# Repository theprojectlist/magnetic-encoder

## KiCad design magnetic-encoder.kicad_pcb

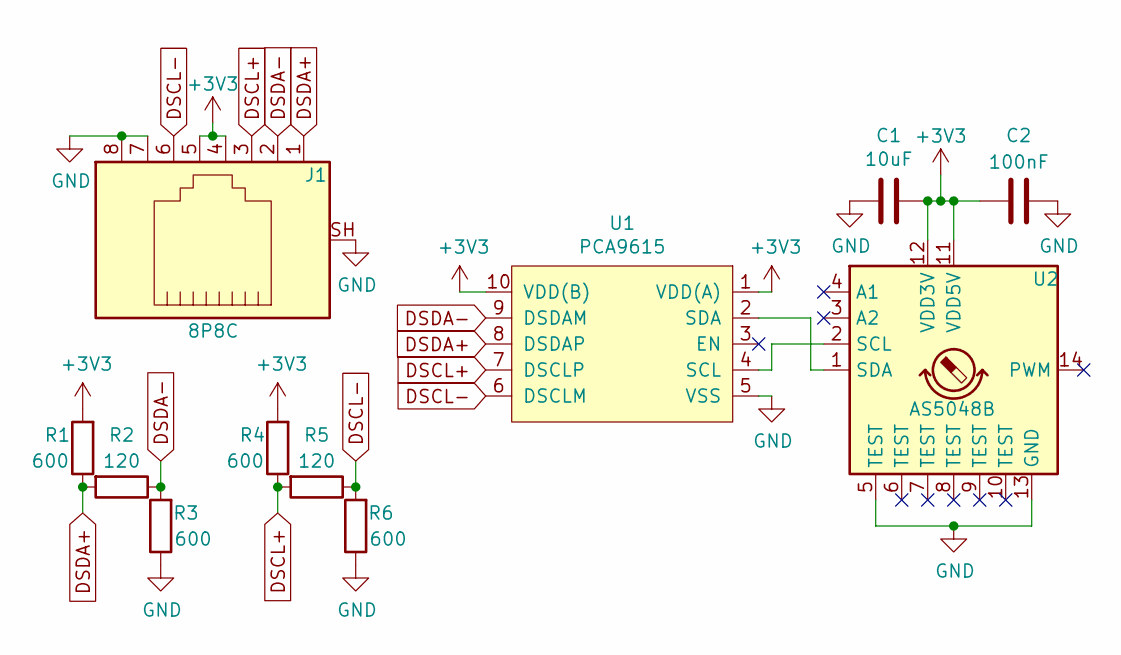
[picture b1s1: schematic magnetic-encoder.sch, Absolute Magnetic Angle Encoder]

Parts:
C1: 10uF; C_0603_1608Metric_Pad1.05x0.95mm_HandSolder
C2: 100nF; C_0603_1608Metric_Pad1.05x0.95mm_HandSolder
J1: 8P8C; RJ45_Amphenol_RJHSE5380
R1, R3, R4, R6: 600; R_0603_1608Metric_Pad1.05x0.95mm_HandSolder
R2, R5: 120; R_0603_1608Metric_Pad1.05x0.95mm_HandSolder
U1: PCA9615; TSSOP-10_3x3mm_P0.5mm
U2: AS5048B; TSSOP-14_4.4x5mm_P0.65mm

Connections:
+3V3: C1.1, C2.2, J1.4, J1.5, R1.2, R4.2, U1.1 (VDD(A)), U1.10 (VDD(B)), U2.11 (VDD5V), U2.12 (VDD3V)
DSCL+: J1.3, R4.1, R5.2, U1.7 (DSCLP)
DSCL-: J1.6, R5.1, R6.2, U1.6 (DSCLM)
DSDA+: J1.1, R1.1, R2.2, U1.8 (DSDAP)
DSDA-: J1.2, R2.1, R3.2, U1.9 (DSDAM)
GND: C1.2, C2.1, J1.7, J1.8, J1.SH, R3.1, R6.1, U1.5 (VSS), U2.5 (TEST), U2.13 (GND)
unnamed: U1.2 (SDA), U2.1 (SDA)
unnamed: U1.4 (SCL), U2.2 (SCL)

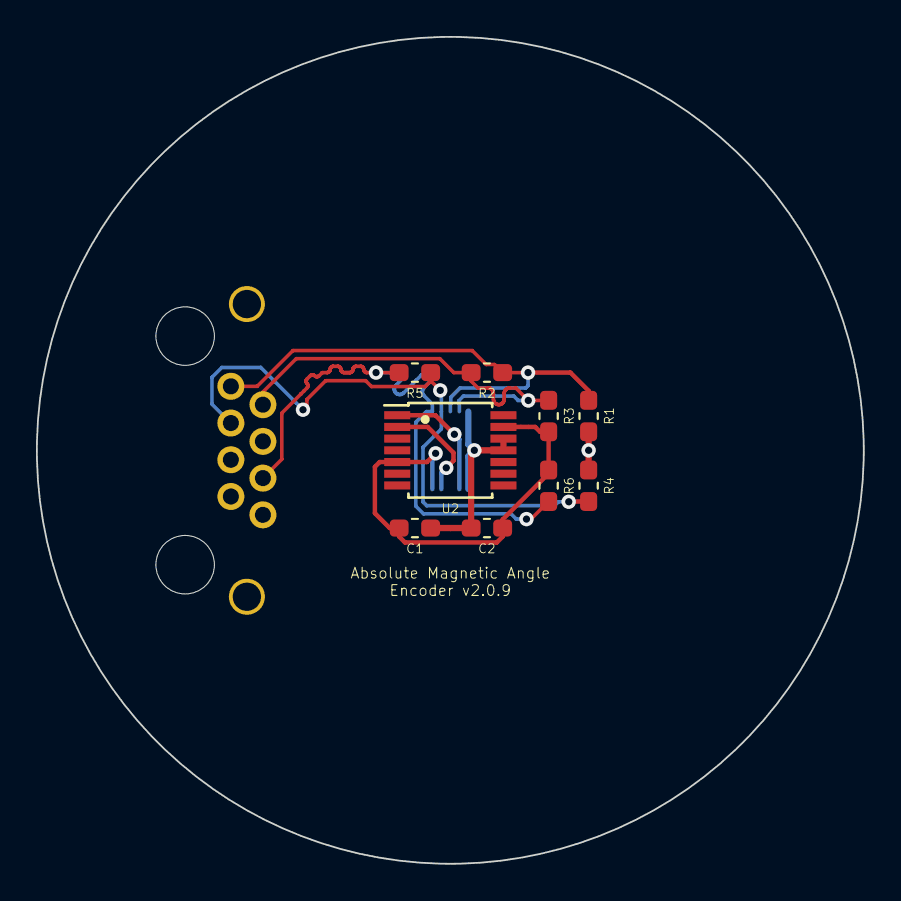
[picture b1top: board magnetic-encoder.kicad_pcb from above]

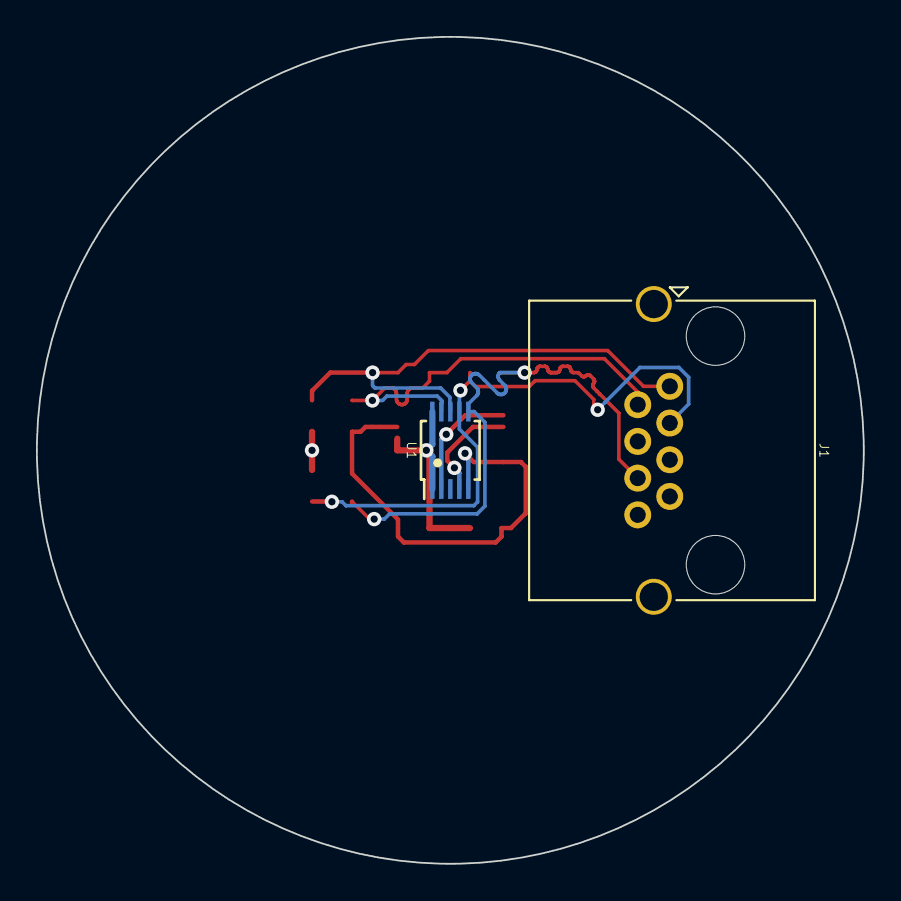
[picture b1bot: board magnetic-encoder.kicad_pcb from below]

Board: 4 copper layers, 45.9 x 45.9 mm, 11 parts (2 on the bottom side), 8 nets.

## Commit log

2020-01-31 Checkpoint hardware revision v2.0.3
2020-02-01 Fix differential tracing
2020-02-05 Add cat5e shielding
